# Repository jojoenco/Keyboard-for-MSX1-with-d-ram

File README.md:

# Keyboard-for-MSX1-with-d-ram

This is the keyboard I created for the MSX1 with D Ram.  
I tested it with the keys only. (because the keycaps are not in yet).  
It works fine.

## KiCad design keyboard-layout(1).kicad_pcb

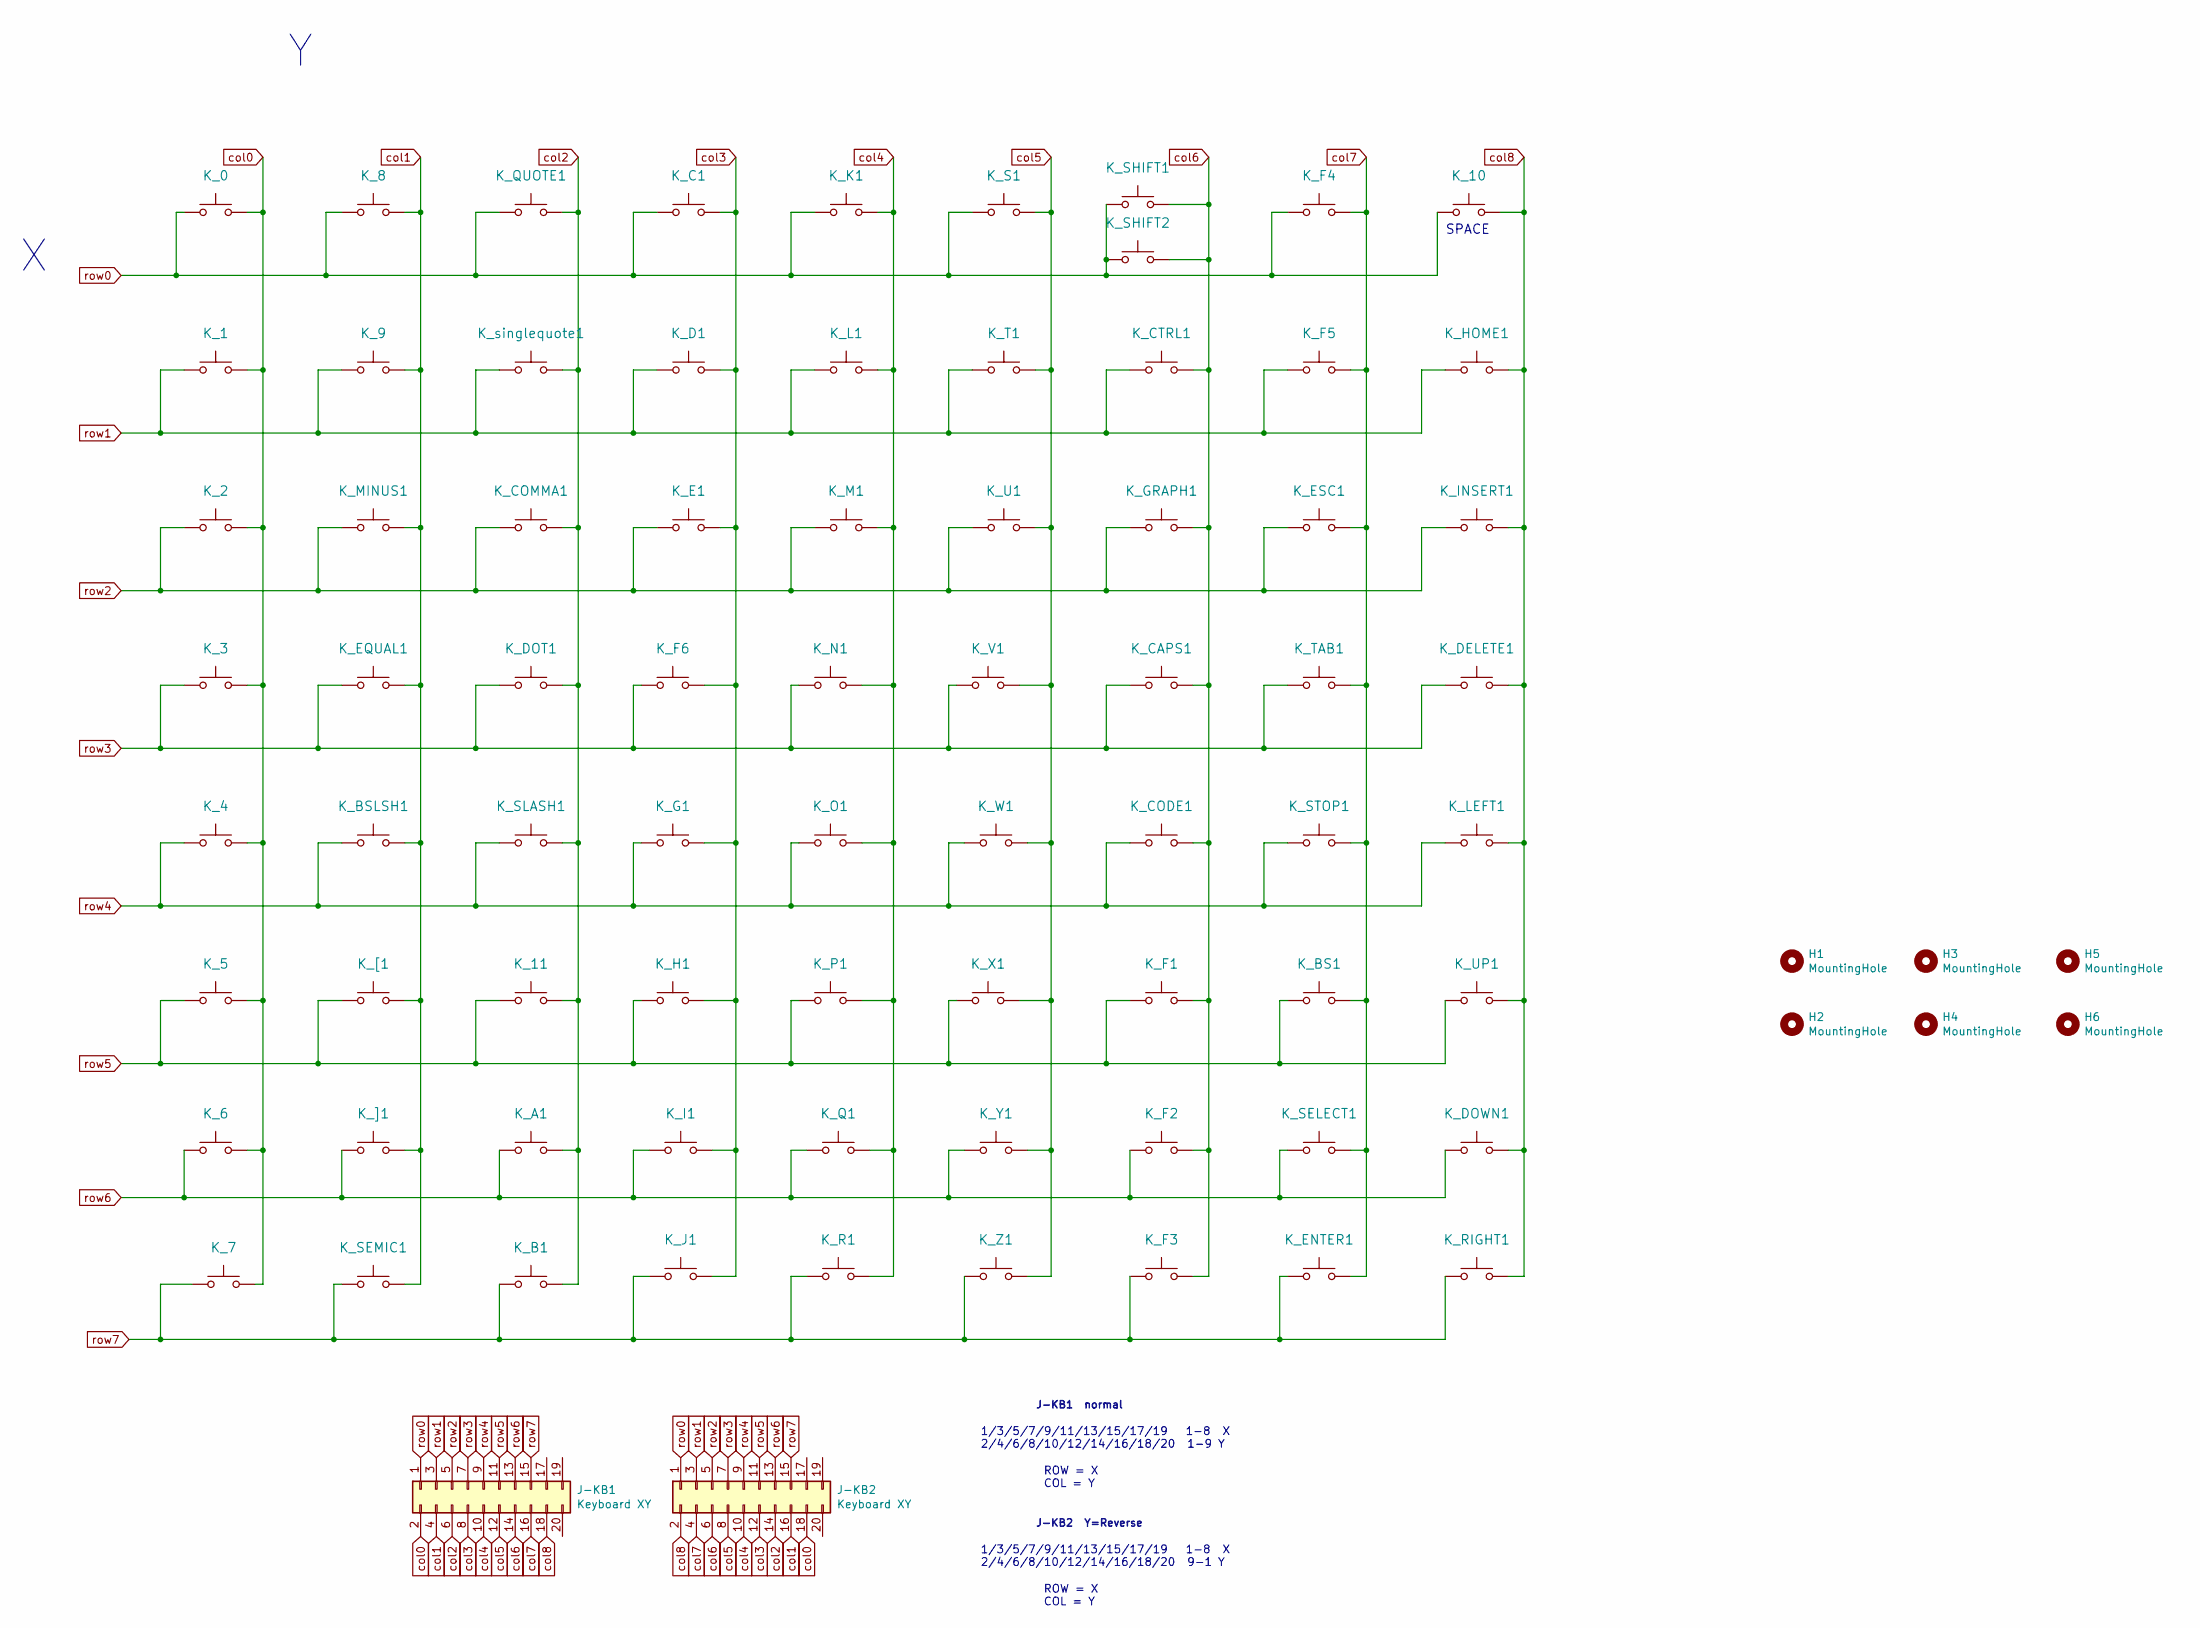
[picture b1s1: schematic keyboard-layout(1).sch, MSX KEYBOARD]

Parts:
H1, H2, H3, H4, H5, H6: MountingHole; MountingHole_4.3mm_M4_DIN965_Pad
J-KB1, J-KB2: Keyboard XY; IDC-Header_2x10_P2.54mm_Vertical
K_0, K_1, K_2, K_3, K_4, K_5, K_6, K_7, K_8, K_9, K_11: KEYSW; MX-1U-NoLED
K_10: KEYSW; MX-6.25U-NoLED
K_A1: KEYSW; MX-1U-NoLED
K_B1: KEYSW; MX-1U-NoLED
K_BS1: KEYSW; MX-1U-NoLED
K_BSLSH1: KEYSW; MX-1U-NoLED
K_C1: KEYSW; MX-1U-NoLED
K_CAPS1: KEYSW; MX-1U-NoLED
K_CODE1: KEYSW; MX-1U-NoLED
K_COMMA1: KEYSW; MX-1U-NoLED
K_CTRL1: KEYSW; MX-1.75U-NoLED
K_D1: KEYSW; MX-1U-NoLED
K_DELETE1: KEYSW; MX-1U-NoLED
K_DOT1: KEYSW; MX-1U-NoLED
K_DOWN1: KEYSW; MX-1U-NoLED
K_E1: KEYSW; MX-1U-NoLED
K_ENTER1: KEYSW; MX-2U-NoLED
K_EQUAL1: KEYSW; MX-1U-NoLED
K_ESC1: KEYSW; MX-1U-NoLED
K_F1, K_F2, K_F3, K_F4, K_F5: KEYSW; MX-2U-NoLED
K_F6: KEYSW; MX-1U-NoLED
K_G1: KEYSW; MX-1U-NoLED
K_GRAPH1: KEYSW; MX-1U-NoLED
K_H1: KEYSW; MX-1U-NoLED
K_HOME1: KEYSW; MX-1U-NoLED
K_I1: KEYSW; MX-1U-NoLED
K_INSERT1: KEYSW; MX-1U-NoLED
K_J1: KEYSW; MX-1U-NoLED
K_K1: KEYSW; MX-1U-NoLED
K_L1: KEYSW; MX-1U-NoLED
K_LEFT1: KEYSW; MX-1U-NoLED
K_M1: KEYSW; MX-1U-NoLED
K_MINUS1: KEYSW; MX-1U-NoLED
K_N1: KEYSW; MX-1U-NoLED
K_O1: KEYSW; MX-1U-NoLED
K_P1: KEYSW; MX-1U-NoLED
K_Q1: KEYSW; MX-1U-NoLED
K_QUOTE1: KEYSW; MX-1U-NoLED
K_R1: KEYSW; MX-1U-NoLED
K_RIGHT1: KEYSW; MX-1U-NoLED
K_S1: KEYSW; MX-1U-NoLED
K_SELECT1: KEYSW; MX-1U-NoLED
K_SEMIC1: KEYSW; MX-1U-NoLED
K_SHIFT1: KEYSW; MX-1.5U-NoLED
K_SHIFT2: KEYSW; MX-2.25U-NoLED
K_SLASH1: KEYSW; MX-1U-NoLED
K_STOP1: KEYSW; MX-2U-NoLED
K_T1: KEYSW; MX-1U-NoLED
K_TAB1: KEYSW; MX-1.5U-NoLED
K_U1: KEYSW; MX-1U-NoLED
K_UP1: KEYSW; MX-1U-NoLED
K_V1: KEYSW; MX-1U-NoLED
K_W1: KEYSW; MX-1U-NoLED
K_X1: KEYSW; MX-1U-NoLED
K_Y1: KEYSW; MX-1U-NoLED
K_Z1: KEYSW; MX-1U-NoLED
K_[1: KEYSW; MX-1U-NoLED
K_]1: KEYSW; MX-1U-NoLED
K_singlequote1: KEYSW; MX-1U-NoLED

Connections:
col0: J-KB1.2, J-KB2.18, K_0.2, K_1.2, K_2.2, K_3.2, K_4.2, K_5.2, K_6.2, K_7.2
col1: J-KB1.4, J-KB2.16, K_8.2, K_9.2, K_BSLSH1.2, K_EQUAL1.2, K_MINUS1.2, K_SEMIC1.2, K_[1.2, K_]1.2
col2: J-KB1.6, J-KB2.14, K_11.2, K_A1.2, K_B1.2, K_COMMA1.2, K_DOT1.2, K_QUOTE1.2, K_SLASH1.2, K_singlequote1.2
col3: J-KB1.8, J-KB2.12, K_C1.2, K_D1.2, K_E1.2, K_F6.2, K_G1.2, K_H1.2, K_I1.2, K_J1.2
col4: J-KB1.10, J-KB2.10, K_K1.2, K_L1.2, K_M1.2, K_N1.2, K_O1.2, K_P1.2, K_Q1.2, K_R1.2
col5: J-KB1.12, J-KB2.8, K_S1.2, K_T1.2, K_U1.2, K_V1.2, K_W1.2, K_X1.2, K_Y1.2, K_Z1.2
col6: J-KB1.14, J-KB2.6, K_CAPS1.2, K_CODE1.2, K_CTRL1.2, K_F1.2, K_F2.2, K_F3.2, K_GRAPH1.2, K_SHIFT1.2, K_SHIFT2.2
col7: J-KB1.16, J-KB2.4, K_BS1.2, K_ENTER1.2, K_ESC1.2, K_F4.2, K_F5.2, K_SELECT1.2, K_STOP1.2, K_TAB1.2
col8: J-KB1.18, J-KB2.2, K_10.2, K_DELETE1.2, K_DOWN1.2, K_HOME1.2, K_INSERT1.2, K_LEFT1.2, K_RIGHT1.2, K_UP1.2
row0: J-KB1.1, J-KB2.1, K_0.1, K_8.1, K_10.1, K_C1.1, K_F4.1, K_K1.1, K_QUOTE1.1, K_S1.1, K_SHIFT1.1, K_SHIFT2.1
row1: J-KB1.3, J-KB2.3, K_1.1, K_9.1, K_CTRL1.1, K_D1.1, K_F5.1, K_HOME1.1, K_L1.1, K_T1.1, K_singlequote1.1
row2: J-KB1.5, J-KB2.5, K_2.1, K_COMMA1.1, K_E1.1, K_ESC1.1, K_GRAPH1.1, K_INSERT1.1, K_M1.1, K_MINUS1.1, K_U1.1
row3: J-KB1.7, J-KB2.7, K_3.1, K_CAPS1.1, K_DELETE1.1, K_DOT1.1, K_EQUAL1.1, K_F6.1, K_N1.1, K_TAB1.1, K_V1.1
row4: J-KB1.9, J-KB2.9, K_4.1, K_BSLSH1.1, K_CODE1.1, K_G1.1, K_LEFT1.1, K_O1.1, K_SLASH1.1, K_STOP1.1, K_W1.1
row5: J-KB1.11, J-KB2.11, K_5.1, K_11.1, K_BS1.1, K_F1.1, K_H1.1, K_P1.1, K_UP1.1, K_X1.1, K_[1.1
row6: J-KB1.13, J-KB2.13, K_6.1, K_A1.1, K_DOWN1.1, K_F2.1, K_I1.1, K_Q1.1, K_SELECT1.1, K_Y1.1, K_]1.1
row7: J-KB1.15, J-KB2.15, K_7.1, K_B1.1, K_ENTER1.1, K_F3.1, K_J1.1, K_R1.1, K_RIGHT1.1, K_SEMIC1.1, K_Z1.1

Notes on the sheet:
1/3/5/7/9/11/13/15/17/19 1-8 X 2/4/6/8/10/12/14/16/18/20 9-1 Y
ROW = X COL = Y
SPACE
1/3/5/7/9/11/13/15/17/19 1-8 X 2/4/6/8/10/12/14/16/18/20 1-9 Y
J-KB2 Y=Reverse
J-KB1 normal

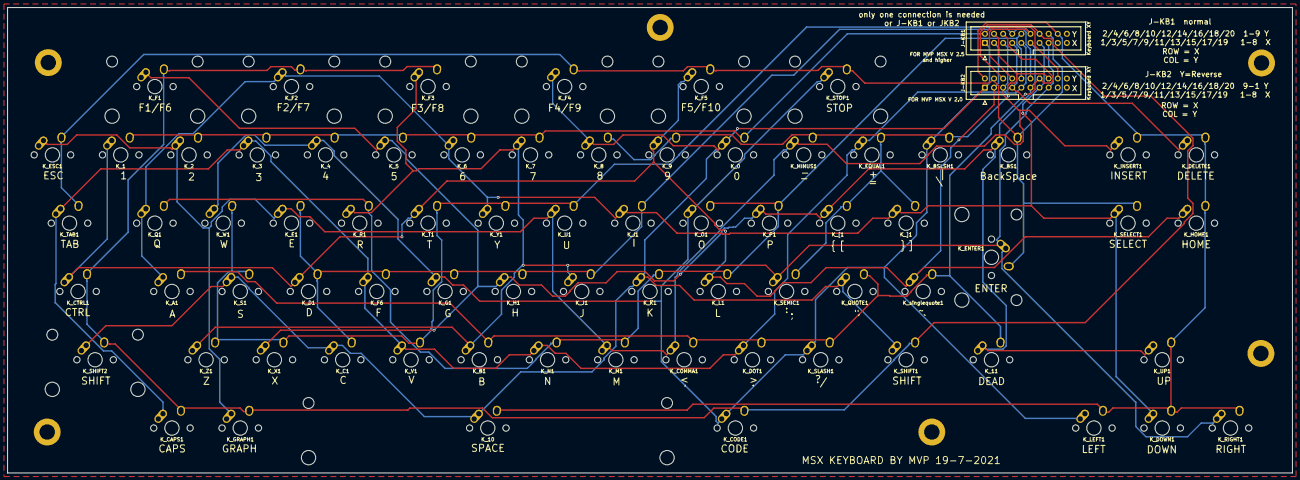
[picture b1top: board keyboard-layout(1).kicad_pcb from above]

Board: 2 copper layers, 358.4 x 129.8 mm, 81 parts (0 on the bottom side), 17 nets.
